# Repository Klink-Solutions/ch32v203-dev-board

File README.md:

# Klink CH32V203 Dev Board

### A compact, breadboard-friendly RISC-V development board built around the
WCH CH32V203K8T6, with USB-C power and programming and built-in LiPo charging.

## Why this exists

Most small dev boards use ARM or ESP32 chips. This board is built on **RISC-V**
(WCH's QingKe core, up to 144 MHz) because of its open source foundation, low price and fast interrupt speeds (it comes with the downside of a less mature development development environment - especially if you wanted to program with the arduino IDE). What started as a XIAO-style board, grew to a larger 17.8 x 49 mm to fit the power path and USB-C. It is also a test bed for the same CH32V203 that I plan to reuse in a later personal project.

It is deliberately kept simple: no Wifi or Bluetooth & no on-board sensors to maintain low power power consumption. The onboard battery circuitry makes it a good alternative for making yor own battery powered devices.

## What it does

* CH32V203K8T6 32-bit RISC-V MCU (LQFP32), 64 KB flash
* USB-C for power, charging and programming
* Single-cell LiPo charging, 100 mA by default, with an optional 2.0 mm JST connector
* Power path: runs from USB when plugged in, from the battery otherwise
* 3.3 V rail: up to 250-350 mA on USB, up to 500 mA on battery
* Resettable fuse on the USB input
* WS2812B RGB LED (works on USB power only) and a charge-status LED
* BOOT and RESET buttons
* Battery voltage readable by firmware (ADC divider)
* 36 breadboard pads with I2C, SPI, UART and more broken out
* 4-layer board, hand-solderable parts

## Version History
* 0.1
    * Initial release 

## Road Map

* Fabrication
* Arduino compatible firmwear
  
## BOM
|Index|Manufacturer Part Number    |Manufacturer Name        |Description                                                                                                                      |Assemblies|Attrition %|Requested Quantity 1|Pack Quantity 1|LCSC Part Number|Unit Price 1|Extended Price 1|Minimum Order Quantity 1|Datasheet                                         |Reference Designator         |
|-----|----------------------------|-------------------------|---------------------------------------------------------------------------------------------------------------------------------|----------|-----------|--------------------|---------------|----------------|------------|----------------|------------------------|--------------------------------------------------|-----------------------------|
|1    |B3U-1000P                   |OMRON                    |Tactile Switch SPST 153gf 1.6mm SMD (SMT) Tab 3mm x 2.5mm Surface Mount                                                          |5         |           |2                   |10             |C231329         |0.1885      |1.89            |5                       |https://www.lcsc.com/product-detail/C231329.html  |BOOT, RESET                  |
|2    |CGA0603X7R104K100JT         |HRE                      |100nF ±10% 10V Ceramic Capacitor X7R 0603                                                                                        |5         |           |7                   |100            |C36911391       |0.0053      |0.53            |100                     |https://www.lcsc.com/product-detail/C36911391.html|C1, C2, C3, C8, C11, C13, C14|
|3    |CGA0603X5R225K100JT         |HRE                      |2.2uF ±10% 10V Ceramic Capacitor X5R 0603                                                                                        |5         |           |3                   |50             |C7503508        |0.0113      |0.57            |50                      |https://www.lcsc.com/product-detail/C7503508.html |C4, C5, C9                   |
|4    |C0603C180F8HACAUTO          |KEMET                    |18pF X8R ±1% 10V 0603 Ceramic Capacitors RoHS                                                                                    |5         |           |2                   |10             |C3882391        |0.1146      |1.15            |5                       |https://www.lcsc.com/product-detail/C3882391.html |C6, C7                       |
|5    |CL10A475KP8NNNC             |Samsung Electro-Mechanics|4.7uF ±10% 10V Ceramic Capacitor X5R 0603                                                                                        |5         |           |2                   |50             |C1705           |0.0133      |0.67            |50                      |https://www.lcsc.com/product-detail/C1705.html    |C10, C12                     |
|6    |PMEG3005EJ,115              |Nexperia                 |Diode 30V 500mA Surface Mount SOD-323F                                                                                           |5         |           |1                   |5              |C552853         |0.1968      |0.98            |5                       |https://www.lcsc.com/product-detail/C552853.html  |D1                           |
|7    |WS2812B-B/W                 |Worldsemi                |SMD5050-4P LED Addressable, Specialty                                                                                            |5         |           |1                   |5              |C114586         |0.1042      |0.52            |5                       |https://www.lcsc.com/product-detail/C114586.html  |D2                           |
|8    |0603L050YR                  |Littelfuse               |Polymeric PTC Resettable Fuse 6V 500mA Surface Mount 0603                                                                        |5         |           |1                   |5              |C207015         |0.194       |0.97            |5                       |https://www.lcsc.com/product-detail/C207015.html  |F1                           |
|9    |CH32V203K8T6                |WCH                      |RISC-V 32 Bit 144MHz LQFP-32(7x7) Microcontrollers                                                                               |5         |           |1                   |5              |C5372188        |0.9843      |4.92            |1                       |https://www.lcsc.com/product-detail/C5372188.html |IC1                          |
|10   |TYPE-C16PIN                 |SHOU HAN                 |USB-C (USB TYPE-C) Receptacle Connector 16 Position Surface Mount, Right Angle                                                   |5         |           |1                   |10             |C393939         |0.0624      |0.62            |10                      |https://www.lcsc.com/product-detail/C393939.html  |J1                           |
|11   |XY-S2B-PH-SM4-TB            |XYECONN                  |Surface Mount, Right Angle PH 250V 2 1 2mm 2A 2P -25℃~+85℃ Tin Beige 1x2P SMD,P=2mm,Surface Mount,Right Angle Headers, Male Pins |5         |           |1                   |10             |C54582899       |0.0419      |0.42            |10                      |https://www.lcsc.com/product-detail/C54582899.html|J2                           |
|12   |APT1608SURCK                |Kingbright               |Red 645nm LED Indication - Discrete 1.95V 0603                                                                                   |5         |           |1                   |5              |C5875723        |0.1264      |0.63            |5                       |https://www.lcsc.com/product-detail/C5875723.html |LED1                         |
|13   |DMG2305UX-7                 |HXY MOSFET               |P-Channel 20V 5A 1.31W Surface Mount SOT-23                                                                                      |5         |           |1                   |20             |C5261054        |0.0376      |0.75            |20                      |https://www.lcsc.com/product-detail/C5261054.html |Q1                           |
|14   |FRC0603J201 TS              |FOJAN                    |200Ω ±5% 100mW 0603 Thick Film Resistor                                                                                          |5         |           |1                   |100            |C2907123        |0.0017      |0.17            |100                     |https://www.lcsc.com/product-detail/C2907123.html |R1                           |
|15   |FRC0603F5101TS              |FOJAN                    |5.1kΩ ±1% 100mW 0603 Thick Film Resistor                                                                                         |5         |           |2                   |200            |C2907044        |0.002       |0.4             |100                     |https://www.lcsc.com/product-detail/C2907044.html |R3, R4                       |
|16   |FRC0603F1002TS              |FOJAN                    |10kΩ ±1% 100mW 0603 Thick Film Resistor                                                                                          |5         |           |1                   |100            |C2906982        |0.002       |0.2             |100                     |https://www.lcsc.com/product-detail/C2906982.html |R7                           |
|17   |FRC0603F1004TS              |FOJAN                    |1MΩ ±1% 100mW 0603 Thick Film Resistor                                                                                           |5         |           |2                   |100            |C2907003        |0.0019      |0.19            |100                     |https://www.lcsc.com/product-detail/C2907003.html |R8, R9                       |
|18   |TLV75733PDBVR               |TI                       |3.3V Positive Fixed SOT-23-5 Voltage Regulators - Linear, Low Drop Out (LDO) Regulators RoHS                                     |5         |           |1                   |5              |C485517         |0.2014      |1.01            |5                       |https://www.lcsc.com/product-detail/C485517.html  |U1                           |
|19   |MCP73831T-2ACI/OT           |MICROCHIP                |3.75V~6V 1 Lithium Battery 550mA SOT-23-5 Battery Chargers RoHS                                                                  |5         |           |1                   |5              |C424093         |0.7761      |3.88            |1                       |https://www.lcsc.com/product-detail/C424093.html  |U2                           |
|20   |NX5032GA-8MHZ-EXS00A-CG07039|NDK                      |Crystal 8MHz ±20ppm 18pF 300Ω SMD5032-2P                                                                                         |5         |           |1                   |5              |C1986270        |0.4898      |2.45            |1                       |https://www.lcsc.com/product-detail/C1986270.html |X1                           |
|21   |PZ254-1-18-Z-8.5            |HCTL                     |Pin Header 18 Position 2.54mm Pitch Single Row Through Hole -40℃~+105℃                                                           |5         |           |2                   |10             |C2894941        |0.2216      |2.22            |5                       |https://www.lcsc.com/product-detail/C2894941.html |                             |
|22   |FRC0603F1003TS              |FOJAN                    |RES 100K OHM 0603                                                                                                                |5         |           |1                   |100            |C2906980        |0.0021      |0.21            |100                     |https://www.lcsc.com/product-detail/C2907123.html |R2                           |
|23   |FRC0603F4701TS              |FOJAN                    |RES 4.7K OHM 0603                                                                                                                |5         |           |3                   |100            |C2907034        |0.0022      |0.22            |100                     |https://www.lcsc.com/product-detail/C2907123.html |R5, R6, R10                  |
|25   |                            |JLC PCB                  |PCB                                                                                                                              |5         |           |5                   |5              |N/A             |            |11.2            |5                       |                                                  |                             |
|     |                            |                         |                                                                                                                                 |5         |           |                    |               |                |3.7814      |36.77           |                        |                                                  |                             |

## Goals

See [`docs/project-goals.md`](docs/project-goals.md).

## Design Requirements

See [`docs/design-requirements.md`](docs/design-requirements.md).

## Repository content

| Path | Contents |
|------|----------|
| [`docs/`](docs/) | Requirements, design notes|
| [`pcb/`](pcb/) | Schematics, layout, CAD, generated outputs |
| [`bom/`](bom/) | Bill of materials |
| [`datasheets/`](datasheets/) | Component datasheets|

## Help

Contact author 

## Author

Lucas Klemmer  
klinksolutions22@gmail.com

## License
MIT LIcense

If anyone ends up reproducing this device or making it even bettter I would be happy to see your improvements and add them to the oficial release.

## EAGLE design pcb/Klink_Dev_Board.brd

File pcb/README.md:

# PCB

Design tool: **Autodesk Fusion** (Electronics / PCB workspace).

Fusion keeps the live design in its cloud project, so this folder holds **exports and
snapshots** of it, committed at meaningful milestones. The commit history here is the
record of how the design evolved.

| Folder | Contents |
|--------|----------|
| `schematics/` | Schematic PDF exports and Fusion design archives (`.f3z`) per milestone |
| `layout/` | Board layout exports (PDF/PNG views, board archives) per milestone |
| `libraries/symbols/` | Custom symbol / library exports |
| `libraries/footprints/` | Custom footprints / package exports |
| `libraries/3d-models/` | 3D models for parts |
| `simulations/` | Simulation files and results |
| `outputs/` | Renders, screenshots, and other generated views (not manufacturing files) |

## Suggested snapshot naming

`<what>_rev<letter>_<YYYY-MM-DD>.<ext>`, e.g. `schematic_revA_2026-10-20.pdf`.

Fabrication outputs (Gerbers, drill, pick-and-place) go in [`../manufacturing/`](../manufacturing/).

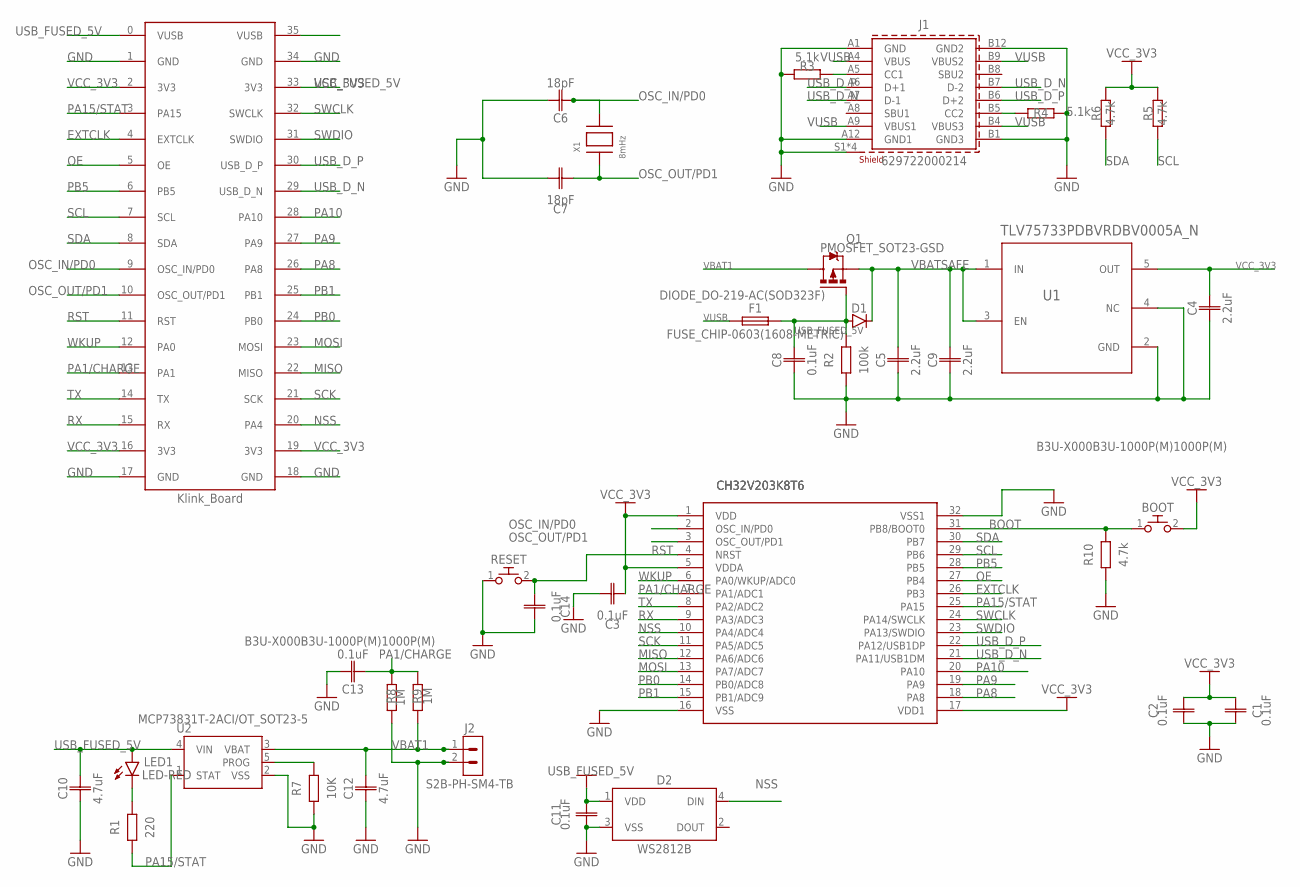
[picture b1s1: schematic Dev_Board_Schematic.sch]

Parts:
BOOT: B3U-X000B3U-1000P(M)1000P(M); B3U-1000P(M)
C1, C2, C3, C8, C11, C13, C14: 0.1uF; CAPC1608X85
C4, C5, C9: 2.2uF; CAPC1608X85
C6, C7: 18pF; CAPC1608X85
C10, C12: 4.7uF; CAPC1608X85
D1: DIODE_DO-219-AC(SOD323F); SODFL2513X70
D2: WS2812B
F1: FUSE_CHIP-0603(1608-METRIC); FUSC1608X60N
IC1: CH32V203K8T6LQFP32; LQFP32-7X7
J1: 629722000214
J2: S2B-PH-SM4-TB
LED1: LED-RED; LEDC1608X39N_R
Q1: PMOSFET_SOT23-GSD; SOT23
R1: 220; RESC1608X60
R2: 100k; RESC1608X60
R3, R4: 5.1k; RESC1608X60
R5, R6, R10: 4.7k; RESC1608X60
R7: 10K; RESC1608X60
R8, R9: 1M; RESC1608X60
RESET: B3U-X000B3U-1000P(M)1000P(M); B3U-1000P(M)
U1: TLV75733PDBVRDBV0005A_N; SOT-23-5
U2: MCP73831T-2ACI/OT_SOT23-5; SOT95P280X110-5
U$1: KLINK_BAORDHYBRID_THROUGH_HOLE; HYBRID_THROUGH_HOLE
X1: 8mHz; NX5032

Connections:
BOOT: BOOT.1, IC1.31 (PB8/BOOT0), R10.2
EXTCLK: IC1.26 (PB3), U$1.4 (EXTCLK)
GND: C1.1, C2.1, C3.2, C4.1, C5.1, C6.2, C7.2, C8.1, C9.1, C10.2, C11.1, C12.2, C13.1, C14.2, D2.3 (VSS), IC1.16 (VSS), IC1.32 (VSS1), J1.A1 (GND), J1.A12 (GND1), J1.B1 (GND3), J1.B12 (GND2), J1.S1 (SHIELD), J1.S2 (SHIELD), J1.S3 (SHIELD), J1.S4 (SHIELD), J2.2, R2.1, R3.2, R4.1, R7.1, R8.1, R10.1, RESET.1, U1.2 (GND), U1.4 (NC), U2.2 (VSS), U$1.1 (GND), U$1.17 (GND), U$1.18 (GND), U$1.34 (GND)
MISO: IC1.12 (PA6/ADC6), U$1.22 (MISO)
MOSI: IC1.13 (PA7/ADC7), U$1.23 (MOSI)
unnamed: J1.B5 (CC2), R4.2
unnamed: J1.A5 (CC1), R3.1
unnamed: LED1.1 (C), R1.2
NSS: D2.4 (DIN), IC1.10 (PA4/ADC4), U$1.20 (PA4)
OE: IC1.27 (PB4), U$1.5 (OE)
OSC_IN/PD0: C6.1, IC1.2 (OSC_IN/PD0), U$1.9 (OSC_IN/PD0), X1.P$2
OSC_OUT/PD1: C7.1, IC1.3 (OSC_OUT/PD1), U$1.10 (OSC_OUT/PD1), X1.P$1
PA1/CHARGE: C13.2, IC1.7 (PA1/ADC1), R8.2, R9.2, U$1.13 (PA1)
PA8: IC1.18 (PA8), U$1.26 (PA8)
PA9: IC1.19 (PA9), U$1.27 (PA9)
PA10: IC1.20 (PA10), U$1.28 (PA10)
PA15/STAT: IC1.25 (PA15), R1.1, U2.1 (STAT), U$1.3 (PA15)
PB0: IC1.14 (PB0/ADC8), U$1.24 (PB0)
PB1: IC1.15 (PB1/ADC9), U$1.25 (PB1)
PB5: IC1.28 (PB5), U$1.6 (PB5)
PROG: R7.2, U2.5 (PROG)
RST: C14.1, IC1.4 (NRST), RESET.2, U$1.11 (RST)
RX: IC1.9 (PA3/ADC3), U$1.15 (RX)
SCK: IC1.11 (PA5/ADC5), U$1.21 (SCK)
SCL: IC1.29 (PB6), R5.1, U$1.7 (SCL)
SDA: IC1.30 (PB7), R6.1, U$1.8 (SDA)
SWCLK: IC1.24 (PA14/SWCLK), U$1.32 (SWCLK)
SWDIO: IC1.23 (PA13/SWDIO), U$1.31 (SWDIO)
TX: IC1.8 (PA2/ADC2), U$1.14 (TX)
USB_D_N: IC1.21 (PA11/USB1DM), J1.A7 (D-1), J1.B7 (D-2), U$1.29 (USB_D_N)
USB_D_P: IC1.22 (PA12/USB1DP), J1.A6 (D+1), J1.B6 (D+2), U$1.30 (USB_D_P)
USB_FUSED_5V: C8.2, C10.1, C11.2, D1.2 (A), D2.1 (VDD), F1.2, LED1.2 (A), Q1.1 (G), R2.2, U2.4 (VIN), U$1.0 (VUSB), U$1.35 (VUSB)
VBAT1: C12.1, J2.1, Q1.3 (D), R9.1, U2.3 (VBAT)
VBATSAFE: C5.2, C9.2, D1.1 (C), Q1.2 (S), U1.1 (IN), U1.3 (EN)
VCC_3V3: BOOT.2, C1.2, C2.2, C3.1, C4.2, IC1.1 (VDD), IC1.5 (VDDA), IC1.17 (VDD1), R5.2, R6.2, U1.5 (OUT), U$1.2 (3V3), U$1.16 (3V3), U$1.19 (3V3), U$1.33 (3V3)
VUSB: F1.1, J1.A4 (VBUS), J1.A9 (VBUS1), J1.B4 (VBUS3), J1.B9 (VBUS2)
WKUP: IC1.6 (PA0/WKUP/ADC0), U$1.12 (PA0)

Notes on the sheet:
CH32V203K8T6

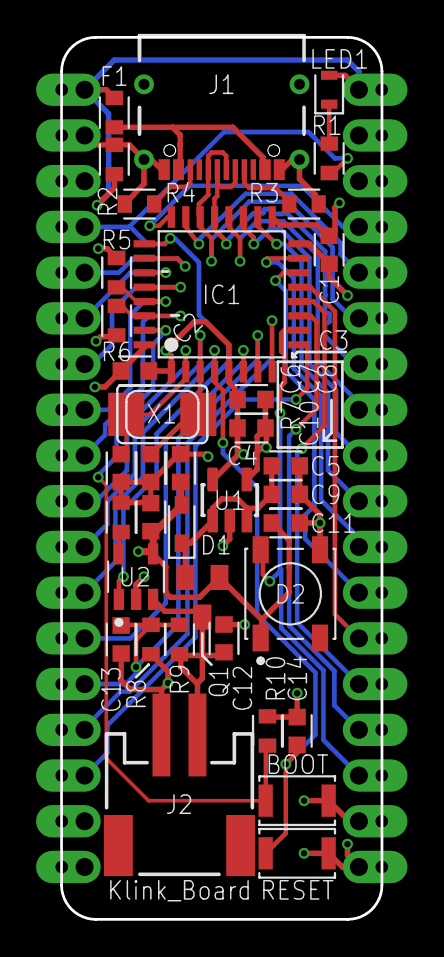
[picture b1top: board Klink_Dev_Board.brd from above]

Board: 4 copper layers, 17.8 x 49.0 mm, 38 parts (0 on the bottom side), 37 nets.

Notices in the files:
parts and their libraries:
Wurth_Connectors_WR-USB: Copyright: Würth Elektronik
